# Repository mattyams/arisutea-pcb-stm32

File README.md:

# THIS IS STILL A WIP! NO GUARANTEES ON ANYTHING!
- [X] v0.3 STM32 PCBs ordered 05/01/21
- [X] Assemble Arisutea PCB once received 05/21/21
- [X] Assemble Acrylic Case to Arisutea STM32 design
- [X] Edit QMK firmware for Arisutea STM32 design
# Arisutea - Arisu Keyboard PCB with More Modifications...now with MORE!
## Disclaimer: Use these files at your own risk.
Fairly confident that this will be the first actual version (v0.3 because...reasons...) of the STM32 version of the Arisutea board. See the notes below on the modification for this version. You will need KiCad 5.99 to view/edit these files.

アリステア PCB designed using KiCad. The layout was originally created by FateNozomi, inspired by Lyn's EM7 and TGR Alice with some modification. The layout was then modified by CorruptedJef and robotictomato to add USB-C, ESD and to shift/add some keys. This inspired me to modify the layout further by adding an STM32 and the ability to swap your switches out whenever you want and to make some keys a little more permenant. I have designed many boards in the past but never a keyboard so this is my first crack at it and I figured why not go all out? If you notice any issue please open an issue and we can discuss!

Since the layout has been modified yet again I decided to give the project a new name, Arisutea, which translates to Alistair. Obviously keeping the theme running here. 

Key modifications to the PCB:
- STM32F072 MCU
  - STM32F102 can be used but a crystal will need to be placed at Y1 (v0.4 - not tested)
- Added in Kailh Hotswap sockets.
- Addition of full backspace position, connected to switch 59 (row 0, column 13).
  - Removed switch 63 and repositioned switch 59 to add full backspace position.
- USB-C ESD rework.
- Added LED indicators for CAPS and NUM lock as well as layer.
- Updated JSON layout file for this particular keyboard.
- Original mounting holes have been returned to their rightful place. The idea of widening them was good at the time for FR4 plates, but not very practical. I am redesigning the case to allow for brass inserts and standoffs to be installed so the PCB will be nice and snug. More on that later. FR4 plates still will work but you will have to drill the holes out manually. If you take this route....go forth cautiously adventurer.

Check out the iBOM [here](https://htmlpreview.github.io/?https://github.com/mattyams/arisutea-pcb-stm32/blob/master/hardware/BOM/arisutea-stm32-ibom.html)! This was generated with [InteractiveHtmlBom](https://github.com/openscopeproject/InteractiveHtmlBom)!

Renders generated by [Tracespace](https://github.com/tracespace/tracespace).

<!--
Just messing around with different switches.

The family, so far....

# Case Files for Ponoko

Case files are updated to reflect changes to the full backspace on switch 59 and can be found in the hardware folder under [arisutea-case](https://github.com/mattyams/arisutea-pcb/tree/master/hardware/arisutea-case).  The case I ordered with these changes just came in this week (3/6/2021) and it works very well with the changes I made to the full backspace and addition of the stablizer on the prototypes designed by CorruptedJef and robotictomato. There is now a "boxed" version of the case that I have made that is designed to work with some wrist rests that do not have the ortho shape. I have not tested this design yet but the prototype should be here this coming week (3/29/2021). There are now case files for version 0.6 that include the indicator LEDs, I have not ordered/tested these but will soon.

# FR4 Plates and Case

Additionaly I have created files for FR4 plates to be made and used with this layout. These can be found in the hardware folder under [FR4_Plates](https://github.com/mattyams/arisutea-pcb/tree/master/hardware/FR4_Plates). The plates are designed to fit with the full backspace and non-stepped capslock. That being said, these will not work on the original Fate Designs PCB. Plates for the LED indicators have not been made just yet, but will be soon.

## Exceprts from original designer, FateNozomi:

Key differences:
- Removed the extra [B] key on the right half and shifted the [NM,.?] row to the left by 0.25U.
- Shifted the 3 keys to the right and added arrow keys.
- Tweaked the bottom so that the 1.5U keys doesn't protrude out a little.

Shifting the [NM,.?] row to the left by 0.25U required quite some work on the arrangement of keys for the right half.
As a result, this does not give the same typing experience as Lyn's EM7 and TGR Alice.
Lyn's EM7 and TGR Alice uses the home row as the center point to vertically align both halves while I used the number row instead.
Due to the nature of staggered keyboards, aligning using the number row resulted in the home row not being aligned.

Disclaimer: Use these files at your own risk.

## Gerber Files
Download the gerber and BOM files under [releases](https://github.com/mattyams/arisutea-pcb/releases).

## PCB Assembly
For the components required, you may refer to the bill of materials included along with the release as reference or load up the design file in KiCad.
All the components can be soldered using a regular soldering iron, though soldering the USB-C receptacle might be the biggest hurdle. I have made an adjustment to the USB footprint to allow for a little more error when handsoldering. If needed, the BOM and POS file can be used on JLCPCB to assemble the PCB although I have not used their service I cannot confirm its accuracy or quality. -->

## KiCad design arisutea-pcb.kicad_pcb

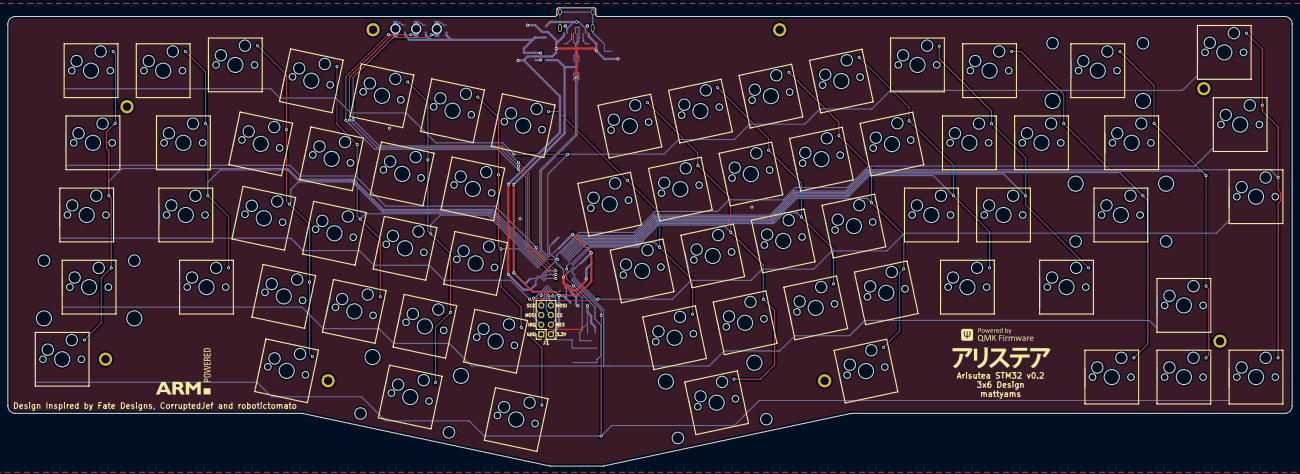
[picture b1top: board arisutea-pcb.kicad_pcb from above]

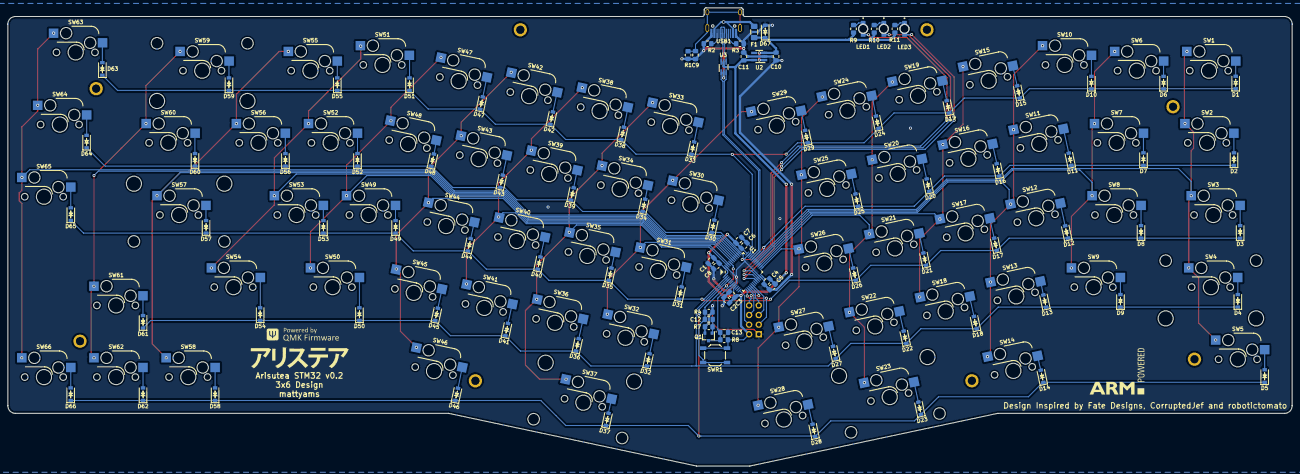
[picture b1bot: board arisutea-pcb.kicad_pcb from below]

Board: 2 copper layers, 339.1 x 121.0 mm, 180 parts (102 on the bottom side), 112 nets.

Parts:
C1, C4, C6, C8, C12, C13: 100n; C_0805_2012Metric_Pad1.18x1.45mm_HandSolder
C2: 10n; C_0805_2012Metric_Pad1.18x1.45mm_HandSolder
C3, C10, C11: 1u; C_0805_2012Metric_Pad1.18x1.45mm_HandSolder
C5, C7: 4.7u; C_0805_2012Metric_Pad1.18x1.45mm_HandSolder
C9: 4.7n; C_0805_2012Metric_Pad1.18x1.45mm_HandSolder
D1, D2, D3, D4, D5, D6, D7, D8, D9, D10, D11, D12, D13, D14, D15, D16, D17, D18, D19, D20, D21, D22, D23, D24, D25, D26, D27, D28, D29, D30, D31, D32, D33, D34, D35, D36, D37, D38, D39, D40, D41, D42, D43, D44, D45, D46, D47, D48, D49, D50, D51, D52, D53, D54, D55, D56, D57, D58, D59, D60, D61, D62, D63, D64, D65, D66: D; D_SOD-123
D67: SMF6.0CA; D_SOD-123
F1: 500mA; Fuse_1206_3216Metric_Pad1.42x1.75mm_HandSolder
H1, H2, H3, H4, H5, H6, H7, H8: ThroughHole; Generic-Mounthole
J1: Conn_Generic_Conn_01x08; PinHeader_2x04_P2.54mm_Vertical
LED1, LED2, LED3: LED; LED_IN-S124ARUW
LOGO1, LOGO2: arisutea_logo
LOGO3, LOGO4: arm_logo; Logo_ARM_powered
LOGO5, LOGO6: qmk_logo; Logo_QMK_Light
Q1: 2N7002; SOT-23
R1: 1M; R_0805_2012Metric_Pad1.20x1.40mm_HandSolder
R2, R3: 5k1; R_0805_2012Metric_Pad1.20x1.40mm_HandSolder
R4, R7, R8: 10K; R_0805_2012Metric_Pad1.20x1.40mm_HandSolder
R9, R10, R11: 470; R_0805_2012Metric_Pad1.20x1.40mm_HandSolder
SW1, SW6, SW7, SW8, SW9, SW10, SW11, SW12, SW13, SW14, SW15, SW16, SW17, SW18, SW19, SW20, SW21, SW22, SW24, SW25, SW26, SW27, SW28, SW29, SW30, SW31, SW32, SW33, SW34, SW35, SW36, SW38, SW39, SW40, SW41, SW42, SW43, SW44, SW45, SW46, SW47, SW48, SW49, SW50, SW51, SW52, SW53, SW55, SW56, SW58, SW61, SW62, SW63, SW64, SW65, SW66: SW_Push; SW_Hotswap_Kailh_1.00u
SW2, SW5, SW60: SW_Push; SW_Hotswap_Kailh_1.50u
SW3, SW54: SW_Push; SW_Hotswap_Kailh_1.75u
SW4: SW_Push; SW_Hotswap_Kailh_2.25u
SW23: SW_Push; SW_Hotswap_Kailh_2.00u_RevStab
SW37: SW_Push; SW_Hotswap_Kailh_2.75u_RevStab
SW57: SW_Push; SW_Hotswap_Kailh_2.25u_RevStab
SW59: SW_Push; SW_Hotswap_Kailh_2.00u
SWR1: SW_Push; SW_SPST_TL3342
U1: STM32F072-LQFP48; LQFP-48_7x7mm_P0.5mm
U2: TLV70233; SOT-23-5_HandSoldering
U3: NUF2221W1T2G; SOT-363_SC-70-6_Handsoldering
USB1: USB_C_HRO_TYPE-C-31-M-12-USB_Type-C; USB_C_Receptacle_HRO_TYPE-C-31-M-12-HandSoldering

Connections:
3.3V: C1.2, C2.2, C3.2, C4.2, C5.2, C6.2, C7.2, C8.2, C11.1, J1.8, R8.1, SWR1.2, U1.1, U1.9, U1.24, U1.36, U1.48, U2.5, U3.5
5V: C10.1, D67.1, F1.1, R9.1, R10.1, R11.1, U2.1, U2.3
D+: U1.33, U3.1
D-: U1.32, U3.3
GND: C1.1, C2.1, C3.1, C4.1, C5.1, C6.1, C7.1, C8.1, C9.2, C10.2, C11.2, C13.2, D67.2, J1.7, Q1.2, R1.2, R2.2, R3.1, R4.2, R7.2, U1.8, U1.23, U1.35, U1.47, U2.2, U3.2, USB1.A1, USB1.A12
NRST: C13.1, Q1.3, R8.2, U1.7
unnamed: C9.1, R1.1, USB1.S1
unnamed: C12.2, Q1.1, R7.1
unnamed: D1.2, SW1.1
unnamed: D2.2, SW2.1
unnamed: D3.2, SW3.1
unnamed: D4.2, SW4.1
unnamed: D5.2, SW5.1
unnamed: D6.2, SW6.1
unnamed: D7.2, SW7.1
unnamed: D8.2, SW8.1
unnamed: D9.2, SW9.1
unnamed: D10.2, SW10.1
unnamed: D11.2, SW11.1
unnamed: D12.2, SW12.1
unnamed: D13.2, SW13.1
unnamed: D14.2, SW14.1
unnamed: D15.2, SW15.1
unnamed: D16.2, SW16.1
unnamed: D17.2, SW17.1
unnamed: D18.2, SW18.1
unnamed: D19.2, SW19.1
unnamed: D20.2, SW20.1
unnamed: D21.2, SW21.1
unnamed: D22.2, SW22.1
unnamed: D23.2, SW23.1
unnamed: D24.2, SW24.1
unnamed: D25.2, SW25.1
unnamed: D26.2, SW26.1
unnamed: D27.2, SW27.1
unnamed: D28.2, SW28.1
unnamed: D29.2, SW29.1
unnamed: D30.2, SW30.1
unnamed: D31.2, SW31.1
unnamed: D32.2, SW32.1
unnamed: D33.2, SW33.1
unnamed: D34.2, SW34.1
unnamed: D35.2, SW35.1
unnamed: D36.2, SW36.1
unnamed: D37.2, SW37.1
unnamed: D38.2, SW38.1
unnamed: D39.2, SW39.1
unnamed: D40.2, SW40.1
unnamed: D41.2, SW41.1
unnamed: D42.2, SW42.1
unnamed: D43.2, SW43.1
unnamed: D44.2, SW44.1
unnamed: D45.2, SW45.1
unnamed: D46.2, SW46.1
unnamed: D47.2, SW47.1
unnamed: D48.2, SW48.1
unnamed: D49.2, SW49.1
unnamed: D50.2, SW50.1
unnamed: D51.2, SW51.1
unnamed: D52.2, SW52.1
unnamed: D53.2, SW53.1
unnamed: D54.2, SW54.1
unnamed: D55.2, SW55.1
unnamed: D56.2, SW56.1
unnamed: D57.2, SW57.1
unnamed: D58.2, SW58.1
unnamed: D59.2, SW59.1
unnamed: D60.2, SW60.1
unnamed: D61.2, SW61.1
unnamed: D62.2, SW62.1
unnamed: D63.2, SW63.1
unnamed: D64.2, SW64.1
unnamed: D65.2, SW65.1
unnamed: D66.2, SW66.1
unnamed: F1.2, USB1.A4, USB1.A9
unnamed: LED1.A, R9.2
unnamed: LED2.A, R10.2
unnamed: LED3.A, R11.2
unnamed: R2.1, USB1.B5
unnamed: R3.2, USB1.A5
unnamed: U3.4, USB1.A7, USB1.B7
unnamed: U3.6, USB1.A6, USB1.B6
SPI_CS: J1.4, U1.14
SPI_IRQ: J1.5, U1.13
SPI_MISO: J1.2, U1.16
SPI_MOSI: J1.3, U1.17
SPI_RES: J1.6, U1.12
SPI_SCK: J1.1, U1.15
boot0: C12.1, R4.1, SWR1.1, U1.44
col0: SW1.2, SW2.2, SW3.2, SW4.2, SW5.2, U1.30
col1: SW6.2, SW7.2, SW8.2, SW9.2, U1.29
col2: SW10.2, SW11.2, SW12.2, SW13.2, SW14.2, U1.28
col3: SW15.2, SW16.2, SW17.2, SW18.2, U1.27
col4: SW19.2, SW20.2, SW21.2, SW22.2, SW23.2, U1.26
col5: SW24.2, SW25.2, SW26.2, SW27.2, SW28.2, U1.25
col6: SW29.2, SW30.2, SW31.2, SW32.2, U1.46
col7: SW33.2, SW34.2, SW35.2, SW36.2, SW37.2, U1.45
col8: SW38.2, SW39.2, SW40.2, SW41.2, U1.43
col9: SW42.2, SW43.2, SW44.2, SW45.2, SW46.2, U1.42
col10: SW47.2, SW48.2, SW49.2, SW50.2, U1.41
col11: SW51.2, SW52.2, SW53.2, SW54.2, U1.40
col12: SW55.2, SW56.2, SW57.2, SW58.2, U1.39
col13: SW59.2, SW60.2, SW61.2, SW62.2, U1.38
col14: SW63.2, SW64.2, SW65.2, SW66.2, U1.37
led1: LED1.C, U1.22
led2: LED2.C, U1.21
led3: LED3.C, U1.20
row0: D1.1, D6.1, D10.1, D15.1, D19.1, D24.1, D29.1, D33.1, D38.1, D42.1, D47.1, D51.1, D55.1, D59.1, D63.1, U1.34
row1: D2.1, D7.1, D11.1, D16.1, D20.1, D25.1, D30.1, D34.1, D39.1, D43.1, D48.1, D52.1, D56.1, D60.1, D64.1, U1.31
row2: D3.1, D8.1, D12.1, D17.1, D21.1, D26.1, D31.1, D35.1, D40.1, D44.1, D49.1, D53.1, D57.1, D65.1, U1.2
row3: D4.1, D9.1, D13.1, D18.1, D22.1, D27.1, D32.1, D36.1, D41.1, D45.1, D50.1, D54.1, D61.1, U1.3
row4: D5.1, D14.1, D23.1, D28.1, D37.1, D46.1, D58.1, D62.1, D66.1, U1.4

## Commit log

2021-04-05 initial STM32 design
2021-04-07 routing and placement work
2021-04-27 big update
    Re-routed everything. Moved components around. Corrected gerbers and BOM/POS. Updated library. Added renders.
2021-05-01 v0.3 for STM32 release
    First version of the STM32 to be sent to JLC for production.
2021-05-10 add firmware
2021-05-22 trace add for ground
2021-07-09 rev0.4 update
    Small update to fix some non critical things.
2021-08-11 Add logo, edit ibom and readme
2021-08-11 Removed arisutea-case to replace with submodule
2021-08-11 Replaced case and fr4-plates directory with submodules
2021-08-11 removed plate gerber files
    These can be found in the plates subfolder gerber folder now.
2021-08-11 Update arisutea-fr4-plates
